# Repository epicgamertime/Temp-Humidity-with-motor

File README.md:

This is a basic project to circulate air inside of the greenhouse in my apartment to prevent mold and fungus flies. 
It uses an Arduino Nano to read a DHT11 temp/humidity sensor and display the readings to a 7-segment LCD. It also has a small DC motor to circulate the air by turning on and off every 15 minutes.

The board has dimensions 53.4mm x 61.5 mm.

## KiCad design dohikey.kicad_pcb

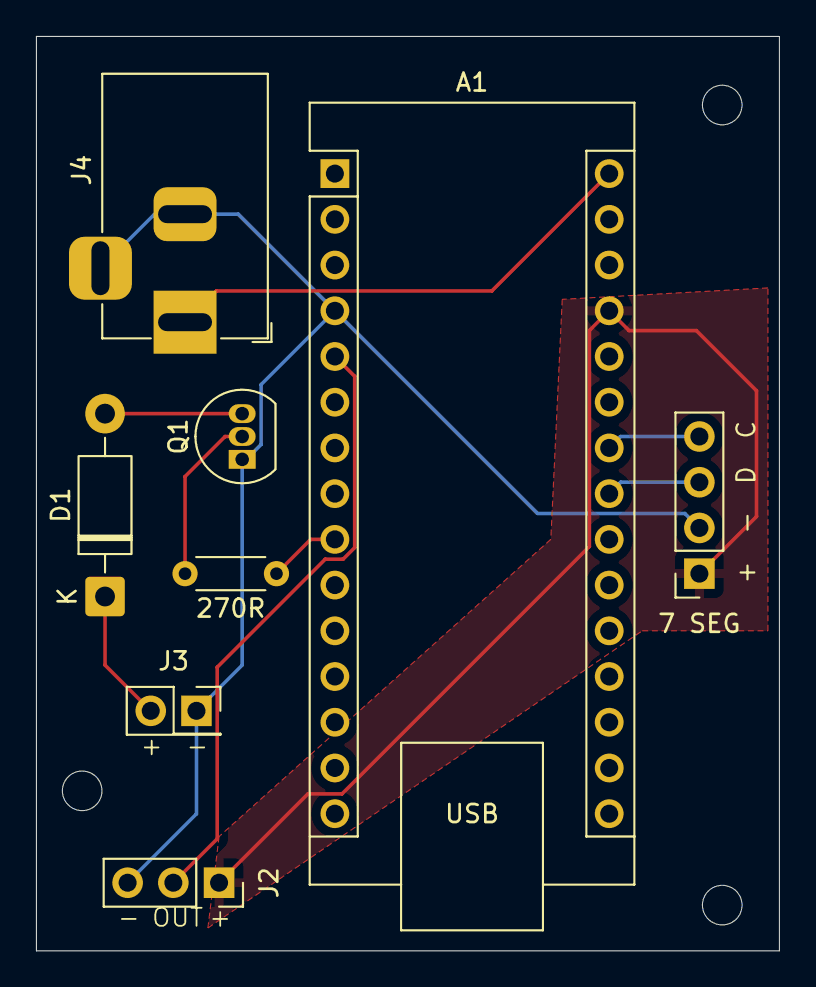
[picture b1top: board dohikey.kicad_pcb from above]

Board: 2 copper layers, 41.3 x 50.8 mm, 11 parts (0 on the bottom side), 10 nets.

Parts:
7 SEG: Conn_01x04_Pin; PinSocket_1x04_P2.54mm_Vertical
270R: 270; R_Axial_DIN0204_L3.6mm_D1.6mm_P5.08mm_Horizontal
A1: Arduino_Nano_v3.x; Arduino_Nano
D1: 1N4001; D_DO-41_SOD81_P10.16mm_Horizontal
H1, H2, H3: MountingHole; MountingHole_2.2mm_M2
J2: DHT11; PinSocket_1x03_P2.54mm_Vertical
J3: Motor; PinSocket_2x01_P2.54mm_Vertical
J4: Barrel_Jack_Switch_Pin3Ring; BarrelJack_Horizontal
Q1: PN2222A; TO-92_Inline

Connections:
+5V: 7 SEG.1, A1.27 (+5V), J2.1
GND: 7 SEG.2, A1.4 (GND), J2.3, J3.1, J4.2, J4.3, Q1.1 (E)
unnamed: 7 SEG.3, A1.23 (A4)
unnamed: 7 SEG.4, A1.24 (A5)
unnamed: A1.5 (D2), J2.2
unnamed: 270R.1, A1.9 (D6)
unnamed: A1.30 (VIN), J4.1
unnamed: D1.2 (A), Q1.3 (C)
unnamed: D1.1 (K), J3.2
unnamed: 270R.2, Q1.2 (B)

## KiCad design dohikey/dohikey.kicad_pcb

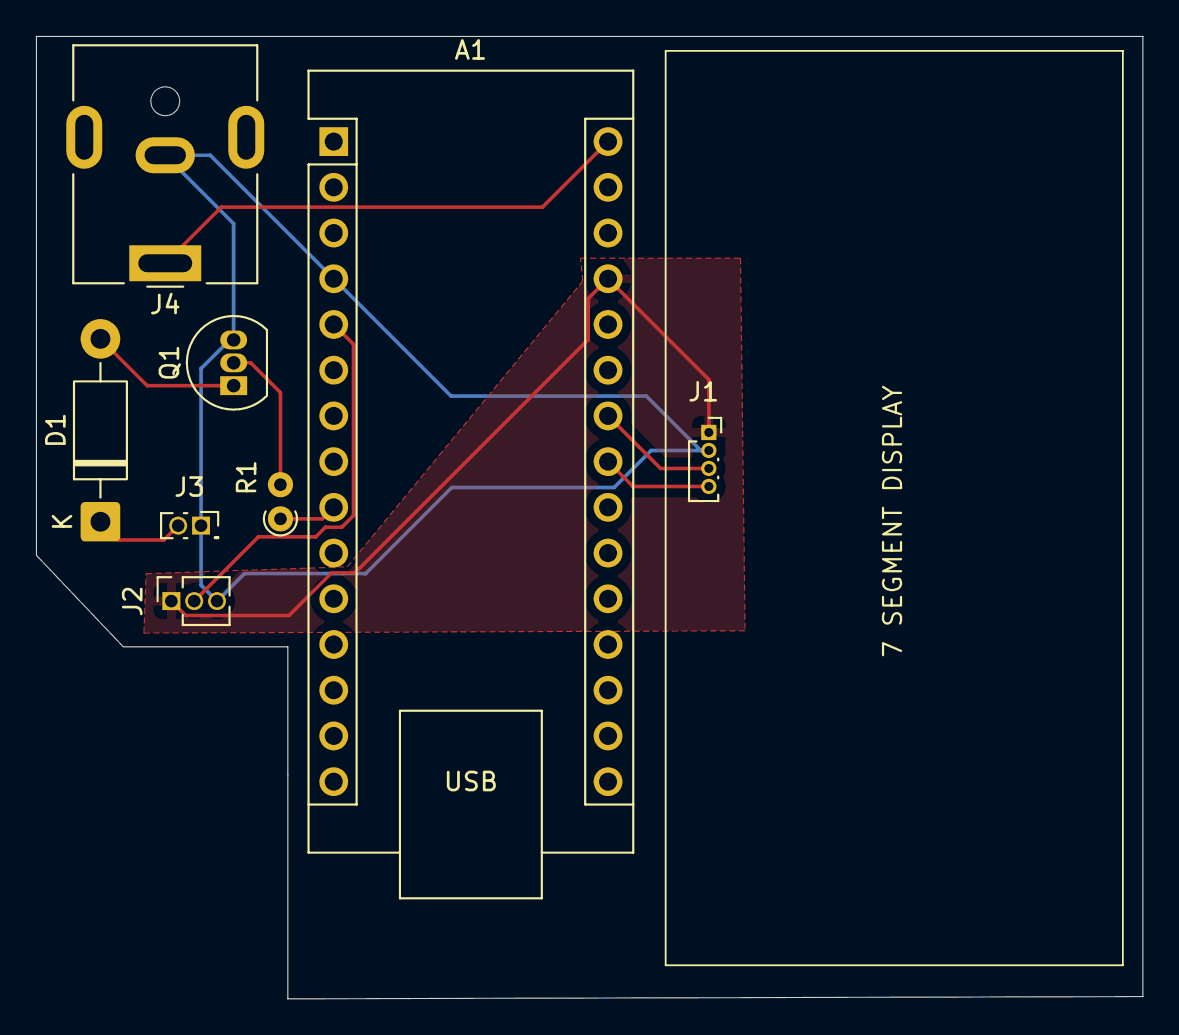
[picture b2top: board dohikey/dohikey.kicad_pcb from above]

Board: 2 copper layers, 61.5 x 53.5 mm, 8 parts (0 on the bottom side), 10 nets.

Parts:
A1: Arduino_Nano_v3.x; Arduino_Nano
D1: 1N4001; D_DO-41_SOD81_P10.16mm_Horizontal
J1: Conn_01x04_Pin; PinSocket_1x04_P1.00mm_Vertical
J2: DHT11; PinSocket_1x03_P1.27mm_Vertical
J3: Motor; PinSocket_2x01_P1.27mm_Vertical
J4: Barrel_Jack_Switch_Pin3Ring; BarrelJack_CUI_PJ-063AH_Horizontal
Q1: PN2222A; TO-92_Inline
R1: 270; R_Axial_DIN0204_L3.6mm_D1.6mm_P1.90mm_Vertical

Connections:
+5V: A1.27 (+5V), J1.1, J2.1
GND: A1.4 (GND), J1.2, J2.3, J3.1, J4.2, Q1.3 (C)
unnamed: A1.23 (A4), J1.4
unnamed: A1.24 (A5), J1.3
unnamed: A1.5 (D2), J2.2
unnamed: A1.9 (D6), R1.1
unnamed: A1.30 (VIN), J4.1
unnamed: D1.2 (A), Q1.1 (E)
unnamed: D1.1 (K), J3.2
unnamed: Q1.2 (B), R1.2

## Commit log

2026-03-08 Add files via upload
    Fixed LCD miswire. Data and Clock pins were swapped.
2026-03-08 Add files via upload
    Add Gerber files and drilling files
